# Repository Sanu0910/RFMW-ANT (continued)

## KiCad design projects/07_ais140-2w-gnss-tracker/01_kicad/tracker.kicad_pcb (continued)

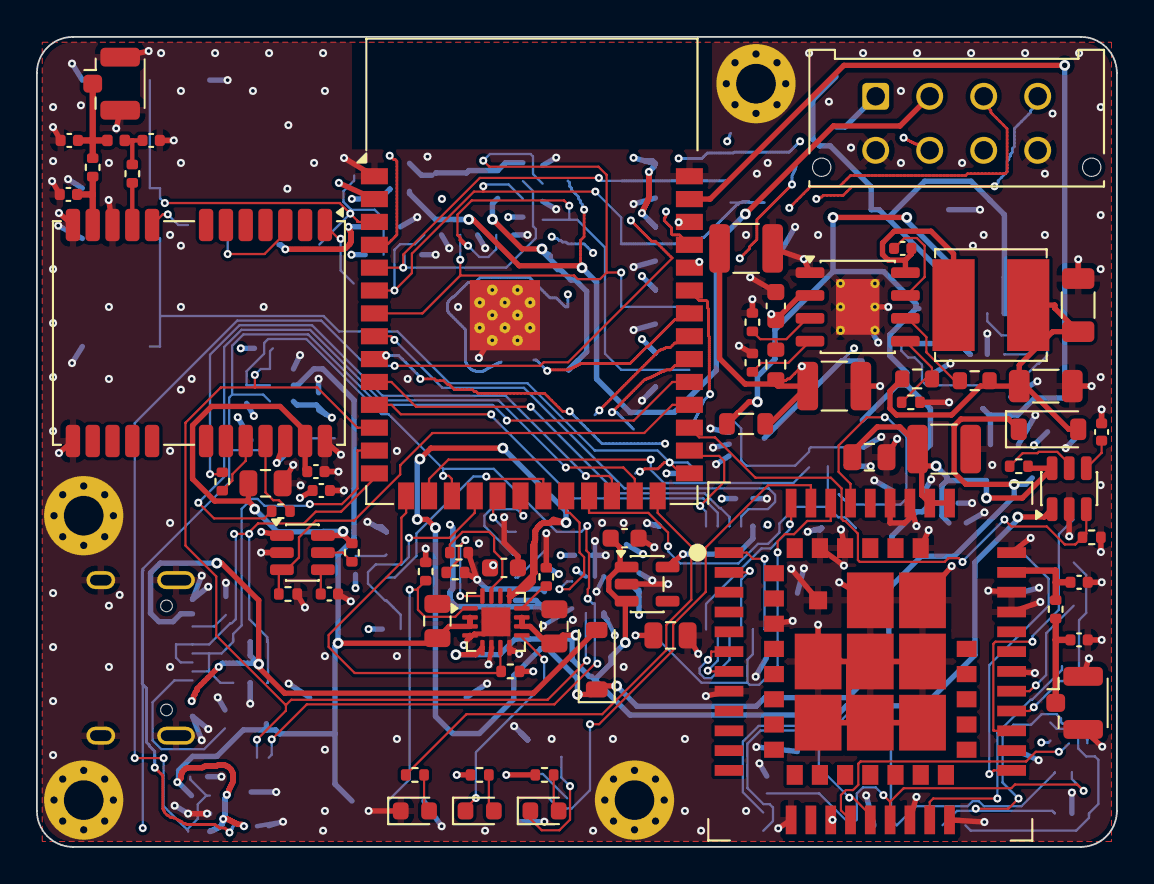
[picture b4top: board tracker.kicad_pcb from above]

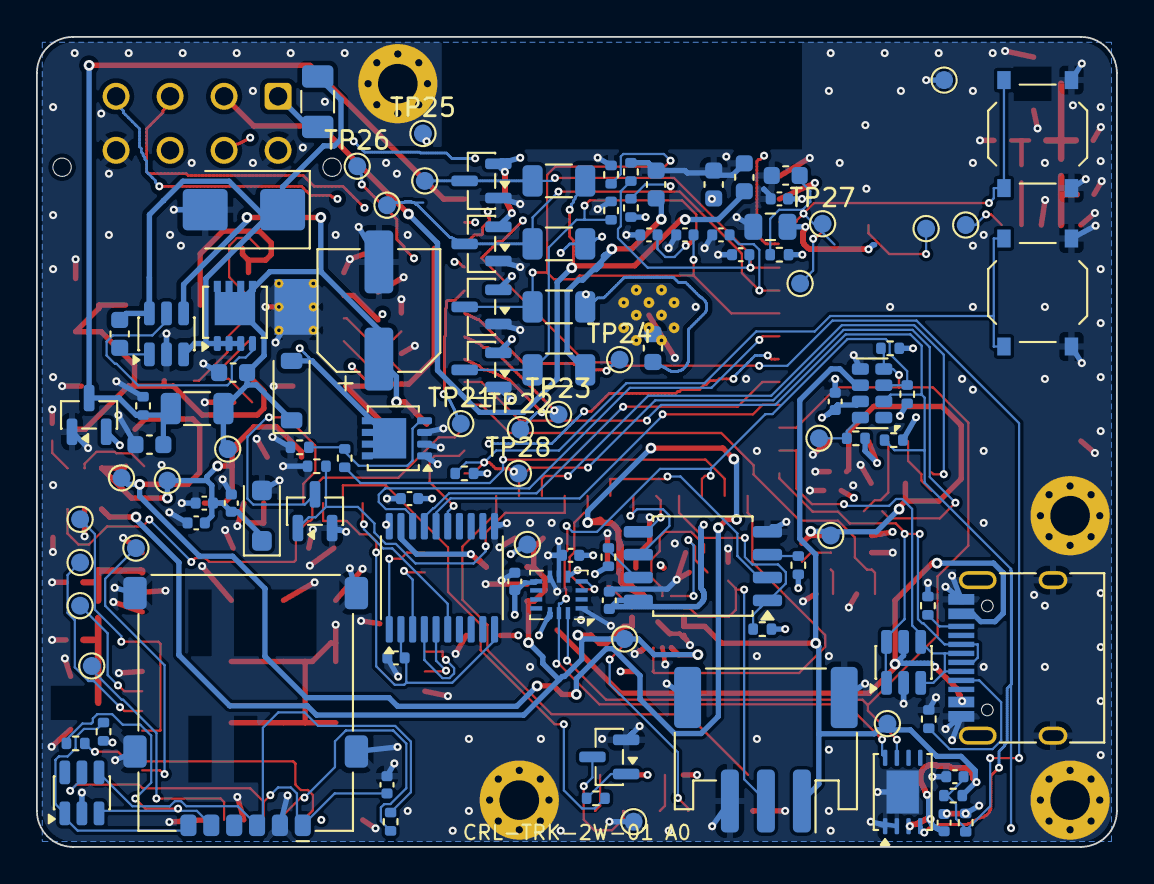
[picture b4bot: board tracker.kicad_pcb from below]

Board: 4 copper layers, 60.0 x 45.0 mm, 180 parts (111 on the bottom side), 114 nets.

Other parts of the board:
TP21: JTAG_TMS; TestPoint_Pad_D1.0mm
TP22: JTAG_TCK; TestPoint_Pad_D1.0mm
TP23: JTAG_TDO; TestPoint_Pad_D1.0mm
TP24: JTAG_TDI; TestPoint_Pad_D1.0mm
TP25: U0TXD; TestPoint_Pad_D1.0mm
TP26: U0RXD; TestPoint_Pad_D1.0mm
TP27: ESP_EN; TestPoint_Pad_D1.0mm
TP28: BOOT; TestPoint_Pad_D1.0mm

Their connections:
BOOT: TP28.1; also elsewhere on the board
ESP_EN: TP27.1; also elsewhere on the board
JTAG_TCK: TP22.1; also elsewhere on the board
JTAG_TDI: TP24.1; also elsewhere on the board
JTAG_TDO: TP23.1; also elsewhere on the board
JTAG_TMS: TP21.1; also elsewhere on the board
U0RXD: TP26.1; also elsewhere on the board
U0TXD: TP25.1; also elsewhere on the board

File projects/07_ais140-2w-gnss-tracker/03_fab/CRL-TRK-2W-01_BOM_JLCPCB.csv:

Comment,Designator,Footprint,LCSC Part #,Manufacturer Part Number
100nF/16V,C1,C_0603_1608Metric,,"0603 MLCC X7R/X5R, AEC-Q200"
100nF/100V,"C2,C6",C_0603_1608Metric,,"0603 MLCC X7R/X5R, AEC-Q200"
22uF/63V,C3,CP_Elec_6.3x7.7,,EEE-FK1J220P
2.2uF/100V,"C4,C5",C_1210_3225Metric,,"1210 MLCC X7R/X5R, AEC-Q200"
2.2nF/50V,C7,C_0402_1005Metric,,"0402 MLCC X7R/X5R, AEC-Q200"
22uF/10V,"C8,C9",C_1206_3216Metric,,"1206 MLCC X7R/X5R, AEC-Q200"
100nF,C10,C_0603_1608Metric,,"0603 MLCC X7R/X5R, AEC-Q200"
1uF/25V,C11,C_0603_1608Metric,,"0603 MLCC X7R/X5R, AEC-Q200"
10uF/10V,"C12,C17,C25,C34",C_0805_2012Metric,,"0805 MLCC X7R/X5R, AEC-Q200"
4.7uF/10V,C13,C_0805_2012Metric,,"0805 MLCC X7R/X5R, AEC-Q200"
100nF,"C14,C15,C21,C23,C26,C29,C30,C31,C35,C36,C40,C41,C42,C44,C46,C48,C50",C_0402_1005Metric,,"0402 MLCC X7R/X5R, AEC-Q200"
1uF/10V,C16,C_0603_1608Metric,,"0603 MLCC X7R/X5R, AEC-Q200"
1nF,"C18,C19",C_0402_1005Metric,,"0402 MLCC X7R/X5R, AEC-Q200"
22uF/10V,C20,C_0805_2012Metric,,"0805 MLCC X7R/X5R, AEC-Q200"
1uF,C22,C_0603_1608Metric,,"0603 MLCC X7R/X5R, AEC-Q200"
100uF/6.3V,C24,C_1210_3225Metric,,"1210 MLCC X7R/X5R, AEC-Q200"
33pF,C27,C_0402_1005Metric,,0402 C0G 50V
10pF,C28,C_0402_1005Metric,,0402 C0G 50V
10nF,C37,C_0402_1005Metric,,"0402 MLCC X7R/X5R, AEC-Q200"
10nF/100V,"C43,C45,C47,C49",C_0603_1608Metric,,"0603 MLCC X7R/X5R, AEC-Q200"
SMBJ33CA,D1,D_SMB,,SMBJ33CA
B5819W,"D2,D4",D_SOD-123,,B5819W
BAT54S,"D3,D9,D10,D11,D12",SOT-23,,BAT54S
GREEN,D5,LED_0603_1608Metric,,LTST-C191KGKT
RED,D6,LED_0603_1608Metric,,LTST-C191KRKT
SMF5.0A,D7,D_SOD-123F,,SMF5.0A
YELLOW,D8,LED_0603_1608Metric,,LTST-C191KSKT
1N4148W,D13,D_SOD-123,,1N4148W-7-F
2A,F1,Fuse_1206_3216Metric,,0466002.NRHF
600R@100M,FB1,L_0805_2012Metric,,BLM21PG601SN1D
VEHICLE 2x4,J1,Molex_Micro-Fit_3.0_43045-0812_2x04_P3.00mm_Vertical,,43045-0812
BATTERY 18650,J2,JST_PH_S3B-PH-SM4-TB_1x03-1MP_P2.00mm_Horizontal,,S3B-PH-SM4-TB(LF)(SN)
USB-C,J3,USB_C_Receptacle_HRO_TYPE-C-31-M-12,,TYPE-C-31-M-12
NANO-SIM,J5,nanoSIM_GCT_SIM8060-6-0-14-00,,SIM8060-6-0-14-00-A
LTE ANT,J6,U.FL_Hirose_U.FL-R-SMT-1_Vertical,,U.FL-R-SMT-1(10)
GNSS ANT,J7,U.FL_Hirose_U.FL-R-SMT-1_Vertical,,U.FL-R-SMT-1(10)
22uH,L1,L_Bourns_SRN6045TA,,SRN6045TA-220M
47nH,L2,L_0402_1005Metric,,LQG15HS47NJ02D
BUK7M12-60EX,Q1,LFPAK33,,BUK7M12-60EX
2N7002,Q2,SOT-23,,2N7002K-7
MMBT3904,Q3,SOT-23,,MMBT3904
BUK9M53-60EX,Q4,LFPAK33,,BUK9M53-60EX
1M,R1,R_0603_1608Metric,,"0603 1% thick film, AEC-Q200"
330k,R2,R_0402_1005Metric,,"0402 1% thick film, AEC-Q200"
160k,R3,R_0402_1005Metric,,"0402 1% thick film, AEC-Q200"
316k,R4,R_0603_1608Metric,,"0603 1% thick film, AEC-Q200"
100k,"R5,R14,R17,R18,R26,R50",R_0402_1005Metric,,"0402 1% thick film, AEC-Q200"
100k,R6,R_0603_1608Metric,,"0603 1% thick film, AEC-Q200"
1M,R7,R_1206_3216Metric,,"1206 1% thick film, AEC-Q200"
68k,R8,R_0402_1005Metric,,"0402 1% thick film, AEC-Q200"
1.5k,R9,R_0402_1005Metric,,"0402 1% thick film, AEC-Q200"
1.78k,R10,R_0402_1005Metric,,"0402 1% thick film, AEC-Q200"
15k,R11,R_0402_1005Metric,,"0402 1% thick film, AEC-Q200"
1M,"R15,R16",R_0402_1005Metric,,"0402 1% thick film, AEC-Q200"
10k,"R19,R20,R23,R37,R40,R48,R53,R54",R_0402_1005Metric,,"0402 1% thick film, AEC-Q200"
5.1k,"R21,R22",R_0402_1005Metric,,"0402 1% thick film, AEC-Q200"
1k,"R24,R25,R28,R33,R34",R_0402_1005Metric,,"0402 1% thick film, AEC-Q200"
4.7k,"R27,R38,R39",R_0402_1005Metric,,"0402 1% thick film, AEC-Q200"
22R,"R29,R30,R31",R_0402_1005Metric,,"0402 1% thick film, AEC-Q200"
0R,"R32,R36",R_0402_1005Metric,,0402 0R jumper
10R,R35,R_0402_1005Metric,,"0402 1% thick film, AEC-Q200"
100k,"R41,R45,R47",R_1206_3216Metric,,"1206 1% thick film, AEC-Q200"
22k,"R42,R46",R_0402_1005Metric,,"0402 1% thick film, AEC-Q200"
4.7k,R43,R_1206_3216Metric,,"1206 1% thick film, AEC-Q200"
47k,R44,R_0402_1005Metric,,"0402 1% thick film, AEC-Q200"
100R,"R49,R51,R52",R_0402_1005Metric,,"0402 1% thick film, AEC-Q200"
RESET,SW1,SW_Push_1P1T_XKB_TS-1187A,,TS-1187A-B-A-B
BOOT,SW2,SW_Push_1P1T_XKB_TS-1187A,,TS-1187A-B-A-B
LM74700-Q1,U1,SOT-23-6,,LM74700QDBVRQ1
LM5164-Q1,U2,HSOP-8-1EP_3.9x4.9mm_P1.27mm_EP2.41x3.1mm_ThermalVias,,LM5164QDDARQ1
BQ24074,U3,VQFN-16-1EP_3x3mm_P0.5mm_EP1.6x1.6mm,,BQ24074RGTR
LC709203F,U4,WDFN-8-1EP_4x3mm_P0.65mm_EP2.4x1.8mm,,LC709203FQH-01TWG
TLV75733P,U5,SOT-23-5,,TLV75733PDBVR
TPS22917,"U6,U7",SOT-23-6,,TPS22917DBVR
ESP32-S3-WROOM-1-N8R2,U8,ESP32-S3-WROOM-1_EdgeAntenna,,ESP32-S3-WROOM-1-N8R2
USBLC6-2SC6,U9,SOT-23-6,,USBLC6-2SC6
W25Q128JV,U10,SOIC-8_5.3x5.3mm_P1.27mm,,W25Q128JVSIQ
SIM7080G,U11,SIMCom_SIM7080G_LCC-77,,SIM7080G
TXS0108E,U12,TSSOP-20_4.4x6.5mm_P0.65mm,,TXS0108EPWR
ESDA6V1-5SC6,U13,SOT-23-6,,ESDA6V1-5SC6
NEO-F10N,U14,ublox_NEO,,NEO-F10N-00B
IIM-42652,U15,Bosch_LGA-14_3x2.5mm_P0.5mm,,IIM-42652
RV-3028-C7,U16,MicroCrystal_C7_SON-8_1.5x3.2mm_P0.9mm,,RV-3028-C7 32.768kHz 1ppm-TA-QC

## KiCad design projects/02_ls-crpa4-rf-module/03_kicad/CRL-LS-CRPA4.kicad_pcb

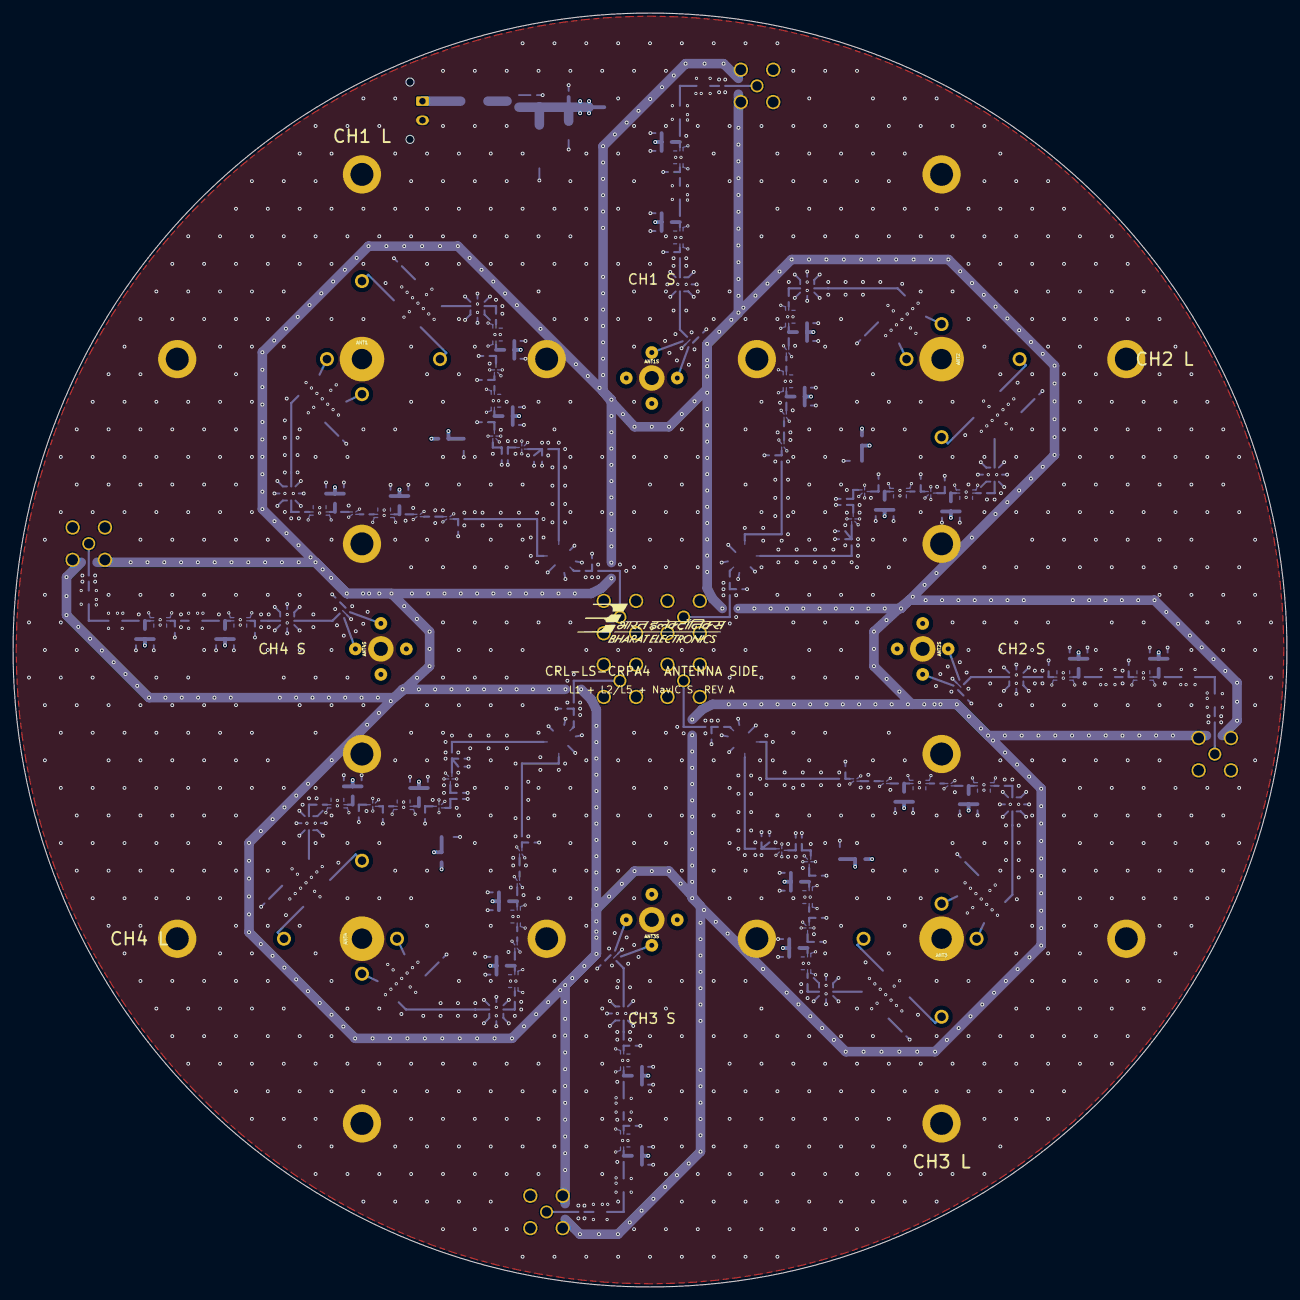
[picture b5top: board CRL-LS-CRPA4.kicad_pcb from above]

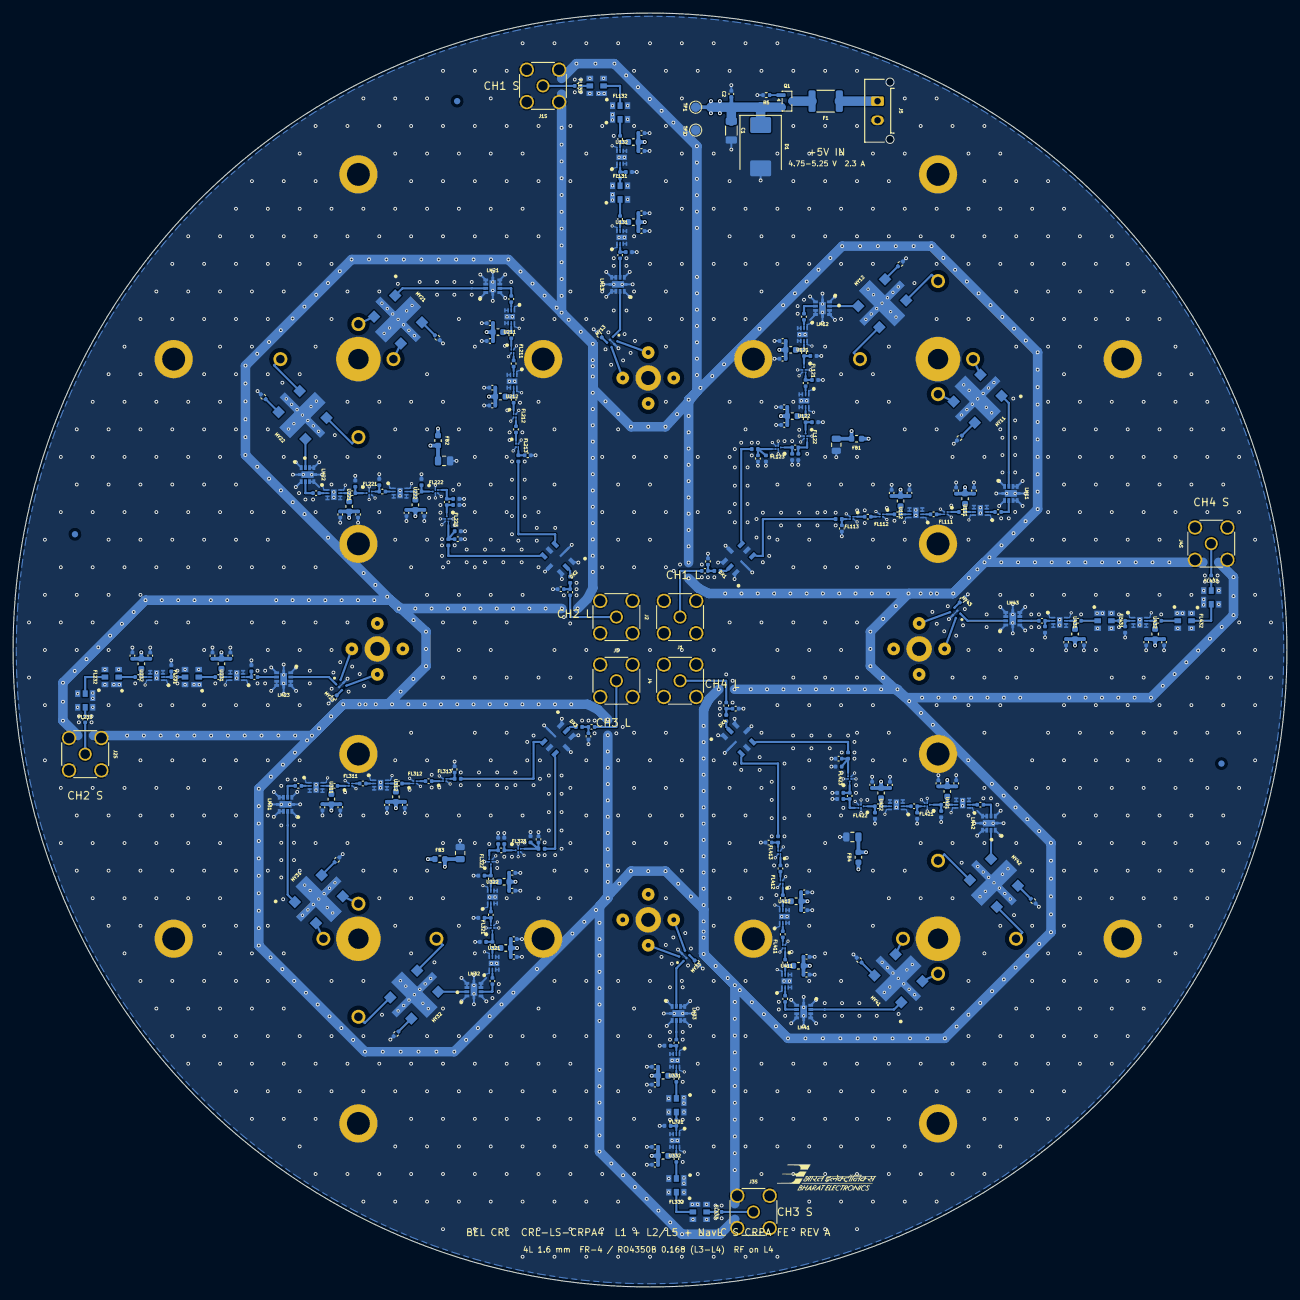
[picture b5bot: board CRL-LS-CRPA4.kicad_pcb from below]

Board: 4 copper layers, 200.0 x 200.0 mm, 331 parts (321 on the bottom side), 209 nets.

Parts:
ANT1, ANT2, ANT3, ANT4: L1/L2 stacked patch; GNSS_StackedPatch_L1L2_4feed
ANT1S, ANT2S, ANT3S, ANT4S: NavIC S patch; NavIC_S_Patch_4feed_combine_model
C1: 22uF; C_1206_3216Metric
C2: 100nF; C_0402_1005Metric
C135, C143, C235, C243, C335, C343, C435, C443, C1111, C1112, C1113, C1121, C1122, C1123, C1131, C1211, C1212, C1213, C1221, C1222, C1223, C1231, C1312, C1313, C1322, C1323, C2111, C2112, C2113, C2121, C2122, C2123, C2131, C2211, C2212, C2213, C2221, C2222, C2223, C2231, C2312, C2313, C2322, C2323, C3111, C3112, C3113, C3121, C3122, C3123, C3131, C3211, C3212, C3213, C3221, C3222, C3223, C3231, C3312, C3313, C3322, C3323, C4111, C4112, C4113, C4121, C4122, C4123, C4131, C4211, C4212, C4213, C4221, C4222, C4223, C4231, C4312, C4313, C4322, C4323: 100pF; C_0402_1005Metric
C141, C241, C341, C441: DNP; C_0402_1005Metric
C142, C242, C342, C442: 1.0pF; C_0402_1005Metric
C144, C244, C344, C444: 1.5pF; C_0402_1005Metric
C190, C290, C390, C490: 10uF; C_0805_2012Metric
C1114, C1124, C1214, C1224, C1314, C1324, C2114, C2124, C2214, C2224, C2314, C2324, C3114, C3124, C3214, C3224, C3314, C3324, C4114, C4124, C4214, C4224, C4314, C4324: 1uF; C_0402_1005Metric
C1311, C1321, C2311, C2321, C3311, C3321, C4311, C4321: 2.4pF; C_0402_1005Metric
D1: 1.5SMC6.8A; D_SMC
DX1, DX2, DX3, DX4: DXP.02.A
F1: 2A hold; Fuse_1812_4532Metric
FB1, FB2, FB3, FB4: 600R@100MHz; L_0603_1608Metric
FID1, FID2, FID3: Fiducial_1mm_Mask2mm
FL111, FL112, FL113, FL211, FL212, FL213, FL311, FL312, FL313, FL411, FL412, FL413: B7504; B7504_SAW_0.9x0.7
FL121, FL122, FL123, FL221, FL222, FL223, FL321, FL322, FL323, FL421, FL422, FL423: B8889; B8889_SAW_1.1x0.9
FL131, FL132, FL133, FL231, FL232, FL233, FL331, FL332, FL333, FL431, FL432, FL433: TA1442A; TA1442A_SAW_3x3
HY11, HY12, HY21, HY22, HY31, HY32, HY41, HY42: HC125A
HY13, HY23, HY33, HY43: C2327J5003AHF; Xinger_C2327J5003AHF
J1, J1S, J2, J2S, J3, J3S, J4, J4S: SMA; SMA_Amphenol_132134_Vertical
J5: +5V IN; Molex_Micro-Fit_3.0_43650-0215_1x02_P3.00mm_Vertical
L111, L112, L121, L122, L211, L212, L221, L222, L311, L312, L321, L322, L411, L412, L421, L422: 18nH; L_0603_1608Metric
L131, L132, L231, L232, L331, L332, L431, L432: 5.6nH; L_0603_1608Metric
L141, L241, L341, L441: 4.7nH; L_0402_1005Metric
L142, L242, L342, L442: 3.3nH; L_0402_1005Metric
L143, L243, L343, L443: 4.3nH; L_0402_1005Metric
L144, L244, L344, L444, L1215, L1216, L1225, L1226, L1235, L2215, L2216, L2225, L2226, L2235, L3215, L3216, L3225, L3226, L3235, L4215, L4216, L4225, L4226, L4235: 6.8nH; L_0402_1005Metric
L1317, L1327, L2317, L2327, L3317, L3327, L4317, L4327: 2.7nH; L_0402_1005Metric
LM11, LM12, LM13, LM21, LM22, LM23, LM31, LM32, LM33, LM41, LM42, LM43: CLM-83-2W+; MiniCircuits_DL1721
LOGOB: BEL_Logo_Silk_Small
LOGOT: BEL_Logo_Silk
MASKT: (no value)
Q1: AO3401A; SOT-23
R5: 10k; R_0402_1005Metric
R11, R12, R13, R21, R22, R23, R31, R32, R33, R41, R42, R43: 49.9R; R_0402_1005Metric
TP1, TP2: TP; TestPoint_Pad_D1.5mm
U111, U112, U121, U122, U131, U132, U211, U212, U221, U222, U231, U232, U311, U312, U321, U322, U331, U332, U411, U412, U421, U422, U431, U432: TQP3M9037; TQP3M9037_DFN8_2x2

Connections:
+5V: C1.1, C2.1, D1.1, FB1.1, FB2.1, FB3.1, FB4.1, Q1.2, TP1.1
+5V_CH1: C190.1, C1113.1, C1114.1, C1123.1, C1124.1, C1213.1, C1214.1, C1223.1, C1224.1, C1313.1, C1314.1, C1323.1, C1324.1, FB1.2, L111.2, L112.2, L121.2, L122.2, L131.2, L132.2
+5V_CH2: C290.1, C2113.1, C2114.1, C2123.1, C2124.1, C2213.1, C2214.1, C2223.1, C2224.1, C2313.1, C2314.1, C2323.1, C2324.1, FB2.2, L211.2, L212.2, L221.2, L222.2, L231.2, L232.2
+5V_CH3: C390.1, C3113.1, C3114.1, C3123.1, C3124.1, C3213.1, C3214.1, C3223.1, C3224.1, C3313.1, C3314.1, C3323.1, C3324.1, FB3.2, L311.2, L312.2, L321.2, L322.2, L331.2, L332.2
+5V_CH4: C490.1, C4113.1, C4114.1, C4123.1, C4124.1, C4213.1, C4214.1, C4223.1, C4224.1, C4313.1, C4314.1, C4323.1, C4324.1, FB4.2, L411.2, L412.2, L421.2, L422.2, L431.2, L432.2
CH1_COM: DX1.2, L143.1
CH1_COM_M: C143.1, C144.1, L143.2
CH1_L1_A1IN: C1111.2, U111.2
CH1_L1_A1OUT: C1112.1, L111.1, U111.7
CH1_L1_A1OUTC: C1112.2, FL111.1
CH1_L1_A2IN: C1121.2, U112.2
CH1_L1_A2OUT: C1122.1, L112.1, U112.7
CH1_L1_A2OUTC: C1122.2, FL112.1
CH1_L1_DXP: DX1.7, L141.2
CH1_L1_F0: ANT1.L1_0, HY11.4
CH1_L1_F90: ANT1.L1_90, HY11.3
CH1_L1_HYB: HY11.1, LM11.2
CH1_L1_ISO: HY11.2, R11.1
CH1_L1_LIM: C1111.1, LM11.7
CH1_L1_S1OUT: C1121.1, FL111.3
CH1_L1_S2OUT: C1131.1, FL112.3
CH1_L1_S3IN: C1131.2, FL113.1
CH1_L1_S3OUT: C141.1, FL113.3, L141.1
CH1_L2_A1IN: C1211.2, U121.2
CH1_L2_A1OUT: C1212.1, L121.1, U121.7
CH1_L2_A1OUTC: C1212.2, FL121.1, L1215.1
CH1_L2_A2IN: C1221.2, U122.2
CH1_L2_A2OUT: C1222.1, L122.1, U122.7
CH1_L2_A2OUTC: C1222.2, FL122.1, L1225.1
CH1_L2_DXP: DX1.5, L142.2
CH1_L2_F0: ANT1.L2_0, HY12.3
CH1_L2_F90: ANT1.L2_90, HY12.4
CH1_L2_HYB: HY12.1, LM12.2
CH1_L2_ISO: HY12.2, R12.1
CH1_L2_LIM: C1211.1, LM12.7
CH1_L2_S1OUT: C1221.1, FL121.4, L1216.1
CH1_L2_S2OUT: C1231.1, FL122.4, L1226.1
CH1_L2_S3IN: C1231.2, FL123.1, L1235.1
CH1_L2_S3OUT: C142.1, FL123.4, L142.1, L144.1
CH1_RFOUT: C143.2, J1.1
CH1_S_A1IN: C1311.2, L1317.1, U131.2
CH1_S_A1OUT: C1312.1, L131.1, U131.7
CH1_S_A1OUTC: C1312.2, FL131.2
CH1_S_A2IN: C1321.2, L1327.1, U132.2
CH1_S_A2OUT: C1322.1, L132.1, U132.7
CH1_S_A2OUTC: C1322.2, FL132.2
CH1_S_F0: ANT1S.F0, HY13.4
CH1_S_F90: ANT1S.F90, HY13.6
CH1_S_HYB: HY13.1, LM13.2
CH1_S_ISO: HY13.3, R13.1
CH1_S_LIM: C1311.1, LM13.7
CH1_S_RFOUT: C135.2, J1S.1
CH1_S_S1OUT: C1321.1, FL131.5
CH1_S_S2OUT: FL132.5, FL133.2
CH1_S_S3OUT: C135.1, FL133.5
CH2_COM: DX2.2, L243.1
CH2_COM_M: C243.1, C244.1, L243.2
CH2_L1_A1IN: C2111.2, U211.2
CH2_L1_A1OUT: C2112.1, L211.1, U211.7
CH2_L1_A1OUTC: C2112.2, FL211.1
CH2_L1_A2IN: C2121.2, U212.2
CH2_L1_A2OUT: C2122.1, L212.1, U212.7
CH2_L1_A2OUTC: C2122.2, FL212.1
CH2_L1_DXP: DX2.7, L241.2
CH2_L1_F0: ANT2.L1_0, HY21.4
CH2_L1_F90: ANT2.L1_90, HY21.3
CH2_L1_HYB: HY21.1, LM21.2
CH2_L1_ISO: HY21.2, R21.1
CH2_L1_LIM: C2111.1, LM21.7
CH2_L1_S1OUT: C2121.1, FL211.3
CH2_L1_S2OUT: C2131.1, FL212.3
CH2_L1_S3IN: C2131.2, FL213.1
CH2_L1_S3OUT: C241.1, FL213.3, L241.1
CH2_L2_A1IN: C2211.2, U221.2
CH2_L2_A1OUT: C2212.1, L221.1, U221.7
CH2_L2_A1OUTC: C2212.2, FL221.1, L2215.1
CH2_L2_A2IN: C2221.2, U222.2
CH2_L2_A2OUT: C2222.1, L222.1, U222.7
CH2_L2_A2OUTC: C2222.2, FL222.1, L2225.1
CH2_L2_DXP: DX2.5, L242.2
CH2_L2_F0: ANT2.L2_0, HY22.3
CH2_L2_F90: ANT2.L2_90, HY22.4
CH2_L2_HYB: HY22.1, LM22.2
CH2_L2_ISO: HY22.2, R22.1
CH2_L2_LIM: C2211.1, LM22.7
CH2_L2_S1OUT: C2221.1, FL221.4, L2216.1
CH2_L2_S2OUT: C2231.1, FL222.4, L2226.1
CH2_L2_S3IN: C2231.2, FL223.1, L2235.1
CH2_L2_S3OUT: C242.1, FL223.4, L242.1, L244.1
CH2_RFOUT: C243.2, J2.1
CH2_S_A1IN: C2311.2, L2317.1, U231.2
CH2_S_A1OUT: C2312.1, L231.1, U231.7
CH2_S_A1OUTC: C2312.2, FL231.2
CH2_S_A2IN: C2321.2, L2327.1, U232.2
CH2_S_A2OUT: C2322.1, L232.1, U232.7
CH2_S_A2OUTC: C2322.2, FL232.2
CH2_S_F0: ANT2S.F0, HY23.4
CH2_S_F90: ANT2S.F90, HY23.6
CH2_S_HYB: HY23.1, LM23.2
CH2_S_ISO: HY23.3, R23.1
CH2_S_LIM: C2311.1, LM23.7
CH2_S_RFOUT: C235.2, J2S.1
CH2_S_S1OUT: C2321.1, FL231.5
CH2_S_S2OUT: FL232.5, FL233.2
CH2_S_S3OUT: C235.1, FL233.5
CH3_COM: DX3.2, L343.1
CH3_COM_M: C343.1, C344.1, L343.2
CH3_L1_A1IN: C3111.2, U311.2
CH3_L1_A1OUT: C3112.1, L311.1, U311.7
CH3_L1_A1OUTC: C3112.2, FL311.1
CH3_L1_A2IN: C3121.2, U312.2
CH3_L1_A2OUT: C3122.1, L312.1, U312.7
CH3_L1_A2OUTC: C3122.2, FL312.1
CH3_L1_DXP: DX3.7, L341.2
CH3_L1_F0: ANT3.L1_0, HY31.4
CH3_L1_F90: ANT3.L1_90, HY31.3
CH3_L1_HYB: HY31.1, LM31.2
CH3_L1_ISO: HY31.2, R31.1
CH3_L1_LIM: C3111.1, LM31.7
CH3_L1_S1OUT: C3121.1, FL311.3
CH3_L1_S2OUT: C3131.1, FL312.3
CH3_L1_S3IN: C3131.2, FL313.1
CH3_L1_S3OUT: C341.1, FL313.3, L341.1
CH3_L2_A1IN: C3211.2, U321.2
CH3_L2_A1OUT: C3212.1, L321.1, U321.7
CH3_L2_A1OUTC: C3212.2, FL321.1, L3215.1
CH3_L2_A2IN: C3221.2, U322.2
CH3_L2_A2OUT: C3222.1, L322.1, U322.7
CH3_L2_A2OUTC: C3222.2, FL322.1, L3225.1
CH3_L2_DXP: DX3.5, L342.2
CH3_L2_F0: ANT3.L2_0, HY32.3
CH3_L2_F90: ANT3.L2_90, HY32.4
CH3_L2_HYB: HY32.1, LM32.2
CH3_L2_ISO: HY32.2, R32.1
CH3_L2_LIM: C3211.1, LM32.7
CH3_L2_S1OUT: C3221.1, FL321.4, L3216.1
CH3_L2_S2OUT: C3231.1, FL322.4, L3226.1
CH3_L2_S3IN: C3231.2, FL323.1, L3235.1
CH3_L2_S3OUT: C342.1, FL323.4, L342.1, L344.1
CH3_RFOUT: C343.2, J3.1
CH3_S_A1IN: C3311.2, L3317.1, U331.2
CH3_S_A1OUT: C3312.1, L331.1, U331.7
CH3_S_A1OUTC: C3312.2, FL331.2
CH3_S_A2IN: C3321.2, L3327.1, U332.2
CH3_S_A2OUT: C3322.1, L332.1, U332.7
CH3_S_A2OUTC: C3322.2, FL332.2
CH3_S_F0: ANT3S.F0, HY33.4
CH3_S_F90: ANT3S.F90, HY33.6
CH3_S_HYB: HY33.1, LM33.2
CH3_S_ISO: HY33.3, R33.1
CH3_S_LIM: C3311.1, LM33.7
CH3_S_RFOUT: C335.2, J3S.1
CH3_S_S1OUT: C3321.1, FL331.5
CH3_S_S2OUT: FL332.5, FL333.2
CH3_S_S3OUT: C335.1, FL333.5
CH4_COM: DX4.2, L443.1
CH4_COM_M: C443.1, C444.1, L443.2
CH4_L1_A1IN: C4111.2, U411.2
CH4_L1_A1OUT: C4112.1, L411.1, U411.7
CH4_L1_A1OUTC: C4112.2, FL411.1
CH4_L1_A2IN: C4121.2, U412.2
CH4_L1_A2OUT: C4122.1, L412.1, U412.7
CH4_L1_A2OUTC: C4122.2, FL412.1
CH4_L1_DXP: DX4.7, L441.2
CH4_L1_F0: ANT4.L1_0, HY41.4
CH4_L1_F90: ANT4.L1_90, HY41.3
CH4_L1_HYB: HY41.1, LM41.2
CH4_L1_ISO: HY41.2, R41.1
CH4_L1_LIM: C4111.1, LM41.7
CH4_L1_S1OUT: C4121.1, FL411.3
CH4_L1_S2OUT: C4131.1, FL412.3
CH4_L1_S3IN: C4131.2, FL413.1
CH4_L1_S3OUT: C441.1, FL413.3, L441.1
CH4_L2_A1IN: C4211.2, U421.2
CH4_L2_A1OUT: C4212.1, L421.1, U421.7
CH4_L2_A1OUTC: C4212.2, FL421.1, L4215.1
CH4_L2_A2IN: C4221.2, U422.2
CH4_L2_A2OUT: C4222.1, L422.1, U422.7
CH4_L2_A2OUTC: C4222.2, FL422.1, L4225.1
CH4_L2_DXP: DX4.5, L442.2
CH4_L2_F0: ANT4.L2_0, HY42.3
CH4_L2_F90: ANT4.L2_90, HY42.4
CH4_L2_HYB: HY42.1, LM42.2
CH4_L2_ISO: HY42.2, R42.1
CH4_L2_LIM: C4211.1, LM42.7
CH4_L2_S1OUT: C4221.1, FL421.4, L4216.1
CH4_L2_S2OUT: C4231.1, FL422.4, L4226.1
CH4_L2_S3IN: C4231.2, FL423.1, L4235.1
CH4_L2_S3OUT: C442.1, FL423.4, L442.1, L444.1
CH4_RFOUT: C443.2, J4.1
CH4_S_A1IN: C4311.2, L4317.1, U431.2
CH4_S_A1OUT: C4312.1, L431.1, U431.7
CH4_S_A1OUTC: C4312.2, FL431.2
CH4_S_A2IN: C4321.2, L4327.1, U432.2
CH4_S_A2OUT: C4322.1, L432.1, U432.7
CH4_S_A2OUTC: C4322.2, FL432.2
CH4_S_F0: ANT4S.F0, HY43.4
CH4_S_F90: ANT4S.F90, HY43.6
CH4_S_HYB: HY43.1, LM43.2
CH4_S_ISO: HY43.3, R43.1
CH4_S_LIM: C4311.1, LM43.7
CH4_S_RFOUT: C435.2, J4S.1
CH4_S_S1OUT: C4321.1, FL431.5
CH4_S_S2OUT: FL432.5, FL433.2
CH4_S_S3OUT: C435.1, FL433.5
GND: ANT1.C, ANT1.M, ANT1S.C, ANT2.C, ANT2.M, ANT2S.C, ANT3.C, ANT3.M, ANT3S.C, ANT4.C, ANT4.M, ANT4S.C, C1.2, C2.2, C141.2, C142.2, C144.2, C190.2, C241.2, C242.2, C244.2, C290.2, C341.2, C342.2, C344.2, C390.2, C441.2, C442.2, C444.2, C490.2, C1113.2, C1114.2, C1123.2, C1124.2, C1213.2, C1214.2, C1223.2, C1224.2, C1313.2, C1314.2, C1323.2, C1324.2, C2113.2, C2114.2, C2123.2, C2124.2, C2213.2, C2214.2, C2223.2, C2224.2, C2313.2, C2314.2, C2323.2, C2324.2, C3113.2, C3114.2, C3123.2, C3124.2, C3213.2, C3214.2, C3223.2, C3224.2, C3313.2, C3314.2, C3323.2, C3324.2, C4113.2, C4114.2, C4123.2, C4124.2, C4213.2, C4214.2, C4223.2, C4224.2, C4313.2, C4314.2, C4323.2, C4324.2, D1.2, DX1.1, DX1.3, DX1.4, DX1.6, DX1.8, DX2.1, DX2.3, DX2.4, DX2.6, DX2.8, DX3.1, DX3.3, DX3.4, DX3.6, DX3.8, DX4.1, DX4.3, DX4.4, DX4.6, DX4.8, FL111.2, FL111.4, FL112.2, FL112.4, FL113.2, FL113.4, FL121.2, FL121.3, FL121.5, FL122.2, FL122.3, FL122.5, FL123.2, FL123.3, FL123.5, FL131.1, FL131.3, FL131.4, FL131.6, FL132.1, FL132.3, FL132.4, FL132.6, FL133.1, FL133.3, FL133.4, FL133.6, FL211.2, FL211.4, FL212.2, FL212.4, FL213.2, FL213.4, FL221.2, FL221.3, FL221.5, FL222.2, FL222.3, FL222.5, FL223.2, FL223.3, FL223.5, FL231.1, FL231.3, FL231.4, FL231.6, FL232.1, FL232.3, FL232.4, FL232.6, FL233.1, FL233.3, FL233.4, FL233.6, FL311.2, FL311.4, FL312.2, FL312.4, FL313.2, FL313.4, FL321.2, FL321.3, FL321.5, FL322.2, FL322.3, FL322.5, FL323.2, FL323.3, FL323.5, FL331.1, FL331.3, FL331.4, FL331.6, FL332.1, FL332.3, FL332.4, FL332.6, FL333.1, FL333.3, FL333.4, FL333.6, FL411.2, FL411.4, FL412.2, FL412.4, FL413.2, FL413.4, FL421.2, FL421.3, FL421.5, FL422.2, FL422.3, FL422.5, FL423.2, FL423.3, FL423.5, FL431.1, FL431.3, FL431.4, FL431.6, FL432.1, FL432.3, FL432.4, FL432.6, FL433.1, FL433.3, FL433.4, FL433.6, HY11.GND, HY12.GND, HY13.2, HY13.5, HY21.GND, HY22.GND, HY23.2, HY23.5, HY31.GND, HY32.GND, HY33.2, HY33.5, HY41.GND, HY42.GND, HY43.2, HY43.5, J1.2, J1S.2, J2.2, J2S.2, J3.2, J3S.2, J4.2, J4S.2, J5.2, L144.2, L244.2, L344.2, L444.2, L1215.2, L1216.2, L1225.2, L1226.2, L1235.2, L1317.2, L1327.2, L2215.2, L2216.2, L2225.2, L2226.2, L2235.2, L2317.2, L2327.2, L3215.2, L3216.2, L3225.2, L3226.2, L3235.2, L3317.2, L3327.2, L4215.2, L4216.2, L4225.2, L4226.2, L4235.2, L4317.2, L4327.2, LM11.1, LM11.3, LM11.4, LM11.5, LM11.6, LM11.8, LM11.9, LM12.1, LM12.3, LM12.4, LM12.5, LM12.6, LM12.8, LM12.9, LM13.1, LM13.3, LM13.4, LM13.5, LM13.6, LM13.8, LM13.9, LM21.1, LM21.3, LM21.4, LM21.5, LM21.6, LM21.8, LM21.9, LM22.1, LM22.3, LM22.4, LM22.5, LM22.6, LM22.8, LM22.9, LM23.1, LM23.3, LM23.4, LM23.5, LM23.6, LM23.8, LM23.9, LM31.1, LM31.3, LM31.4, LM31.5, LM31.6, LM31.8, LM31.9, LM32.1, LM32.3, LM32.4, LM32.5, LM32.6, LM32.8, LM32.9, LM33.1, LM33.3, LM33.4, LM33.5, LM33.6, LM33.8, LM33.9, LM41.1, LM41.3, LM41.4, LM41.5, LM41.6, LM41.8, LM41.9, LM42.1, LM42.3, LM42.4, LM42.5, LM42.6, LM42.8, LM42.9, LM43.1, LM43.3, LM43.4, LM43.5, LM43.6, LM43.8, LM43.9, R5.2, R11.2, R12.2, R13.2, R21.2, R22.2, R23.2, R31.2, R32.2, R33.2, R41.2, R42.2, R43.2, TP2.1, U111.1, U111.3, U111.4, U111.5, U111.6, U111.8, U111.9, U112.1, U112.3, U112.4, U112.5, U112.6, U112.8, U112.9, U121.1, U121.3, U121.4, U121.5, U121.6, U121.8, U121.9, U122.1, U122.3, U122.4, U122.5, U122.6, U122.8, U122.9, U131.1, U131.3, U131.4, U131.5, U131.6, U131.8, U131.9, U132.1, U132.3, U132.4, U132.5, U132.6, U132.8, U132.9, U211.1, U211.3, U211.4, U211.5, U211.6, U211.8, U211.9, U212.1, U212.3, U212.4, U212.5, U212.6, U212.8, U212.9, U221.1, U221.3, U221.4, U221.5, U221.6, U221.8, U221.9, U222.1, U222.3, U222.4, U222.5, U222.6, U222.8, U222.9, U231.1, U231.3, U231.4, U231.5, U231.6, U231.8, U231.9, U232.1, U232.3, U232.4, U232.5, U232.6, U232.8, U232.9, U311.1, U311.3, U311.4, U311.5, U311.6, U311.8, U311.9, U312.1, U312.3, U312.4, U312.5, U312.6, U312.8, U312.9, U321.1, U321.3, U321.4, U321.5, U321.6, U321.8, U321.9, U322.1, U322.3, U322.4, U322.5, U322.6, U322.8, U322.9, U331.1, U331.3, U331.4, U331.5, U331.6, U331.8, U331.9, U332.1, U332.3, U332.4, U332.5, U332.6, U332.8, U332.9, U411.1, U411.3, U411.4, U411.5, U411.6, U411.8, U411.9, U412.1, U412.3, U412.4, U412.5, U412.6, U412.8, U412.9, U421.1, U421.3, U421.4, U421.5, U421.6, U421.8, U421.9, U422.1, U422.3, U422.4, U422.5, U422.6, U422.8, U422.9, U431.1, U431.3, U431.4, U431.5, U431.6, U431.8, U431.9, U432.1, U432.3, U432.4, U432.5, U432.6, U432.8, U432.9
QG: Q1.1, R5.1
VIN: F1.1, J5.1
VIN_F: F1.2, Q1.3

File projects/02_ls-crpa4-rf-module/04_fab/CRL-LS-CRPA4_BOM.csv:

item,qty,refs,value,mpn,manufacturer,footprint,side,description
1,4,C142 C242 C342 C442,1.0pF,GJM1555C1H1R0BB01D,Murata,C_0402_1005Metric,bottom,C0G hi-Q 0402
2,4,C144 C244 C344 C444,1.5pF,GJM1555C1H1R5BB01D,Murata,C_0402_1005Metric,bottom,C0G hi-Q 0402
3,8,C1311 C1321 C2311 C2321 C3311 C3321 C4311 C4321,2.4pF,GJM1555C1H2R4BB01D,Murata,C_0402_1005Metric,bottom,"C0G hi-Q 0402, S LNA input series (Qorvo 2.3-2.6 GHz ref. design)"
4,80,C1111 C1112 C1113 C1121 C1122 C1123 C1131 C1211 C1212 C1213 C1221 C1222 C1223 C1231 C1312 C1313 C1322 C1323 C135 C143 C2111 C2112 C2113 C2121 C2122 C2123 C2131 C2211 C2212 C2213 C2221 C2222 C2223 C2231 C2312 C2313 C2322 C2323 C235 C243 C3111 C3112 C3113 C3121 C3122 C3123 C3131 C3211 C3212 C3213 C3221 C3222 C3223 C3231 C3312 C3313 C3322 C3323 C335 C343 C4111 C4112 C4113 C4121 C4122 C4123 C4131 C4211 C4212 C4213 C4221 C4222 C4223 C4231 C4312 C4313 C4322 C4323 C435 C443,100pF,GRM1555C1H101JA01D,Murata,C_0402_1005Metric,bottom,C0G 50 V 0402
5,24,C1114 C1124 C1214 C1224 C1314 C1324 C2114 C2124 C2214 C2224 C2314 C2324 C3114 C3124 C3214 C3224 C3314 C3324 C4114 C4124 C4214 C4224 C4314 C4324,1uF,GRM155R61A105KE15D,Murata,C_0402_1005Metric,bottom,X5R 10 V 0402
6,1,C2,100nF,GRM155R71C104KA88D,Murata,C_0402_1005Metric,bottom,X7R 16 V 0402
7,4,C190 C290 C390 C490,10uF,GRM21BR61A106KE19L,Murata,C_0805_2012Metric,bottom,X5R 10 V 0805
8,1,C1,22uF,GRM31CR61A226KE15L,Murata,C_1206_3216Metric,bottom,X5R 10 V 1206
9,1,D1,1.5SMC6.8A,1.5SMC6.8A,Littelfuse,D_SMC,bottom,"TVS 1500 W, 5.8 V standoff / 6.8 V breakdown, SMC (DO-214AB)"
10,4,DX1 DX2 DX3 DX4,DXP.02.A,DXP.02.A,Taoglas,DXP.02.A,bottom,GNSS diplexer L1 / L2-L5
11,12,FL121 FL122 FL123 FL221 FL222 FL223 FL321 FL322 FL323 FL421 FL422 FL423,B8889,B39122B8889P810,Qualcomm RF360,B8889_SAW_1.1x0.9,bottom,"SAW, GNSS L2/L5"
12,12,FL111 FL112 FL113 FL211 FL212 FL213 FL311 FL312 FL313 FL411 FL412 FL413,B7504,B39162B7504L210,Qualcomm RF360,B7504_SAW_0.9x0.7,bottom,"SAW, GNSS L1/B1/G1"
13,4,FB1 FB2 FB3 FB4,600R@100MHz,BLM18KG601SN1D,Murata,L_0603_1608Metric,bottom,"ferrite bead 1.3 A, per-channel bias isolation (star branch)"
14,1,F1,2A hold,MF-MSMF200-2,Bourns,Fuse_1812_4532Metric,bottom,resettable fuse 1812
15,12,FL131 FL132 FL133 FL231 FL232 FL233 FL331 FL332 FL333 FL431 FL432 FL433,TA1442A,TA1442A,Tai-Saw,TA1442A_SAW_3x3,bottom,"SAW 2492 MHz NavIC S, 3.0x3.0x1.4 mm, IL 1.55 dB, Pin max +10 dBm, DC max 3 V (Tai-Saw Rev 1 land pattern)"
16,4,HY13 HY23 HY33 HY43,C2327J5003AHF,C2327J5003AHF,TTM Technologies,Xinger_C2327J5003AHF,bottom,"Xinger 90 deg hybrid 2300-2700 MHz, IL 0.3 dB, iso 22 dB, 0.68 mm (TTM Rev K land pattern); config 1: F0 -> 4, F90 -> 6 = RHCP"
17,8,HY11 HY12 HY21 HY22 HY31 HY32 HY41 HY42,HC125A,HC125A,Taoglas,HC125A,bottom,90 deg hybrid coupler 1150-1630 MHz
18,8,J1 J1S J2 J2S J3 J3S J4 J4S,SMA,132134,Amphenol RF,SMA_Amphenol_132134_Vertical,bottom,"SMA jack, vertical PCB, 50 ohm (fitted on bottom)"
19,1,J5,+5V IN,43650-0215,Molex,Molex_Micro-Fit_3.0_43650-0215_1x02_P3.00mm_Vertical,bottom,"Micro-Fit 3.0, 2 pos, single DC bias input"
20,12,LM11 LM12 LM13 LM21 LM22 LM23 LM31 LM32 LM33 LM41 LM42 LM43,CLM-83-2W+,CLM-83-2W+,Mini-Circuits,MiniCircuits_DL1721,bottom,"RF limiter 30-8200 MHz, 2 W, +11.5 dBm out, DL1721 3x3 mm hermetic"
21,8,L1317 L1327 L2317 L2327 L3317 L3327 L4317 L4327,2.7nH,LQP15MN2N7B02D,Murata,L_0402_1005Metric,bottom,S LNA input shunt (Qorvo 2.3-2.6 GHz ref. design) [verify MPN]
22,4,L142 L242 L342 L442,3.3nH,LQW15AN3N3B00D,Murata,L_0402_1005Metric,bottom,DXP L2/L5 port series
23,4,L143 L243 L343 L443,4.3nH,LQW15AN4N3B00D,Murata,L_0402_1005Metric,bottom,DXP common port series
24,4,L141 L241 L341 L441,4.7nH,LQW15AN4N7B00D,Murata,L_0402_1005Metric,bottom,DXP L1 port series
25,24,L1215 L1216 L1225 L1226 L1235 L144 L2215 L2216 L2225 L2226 L2235 L244 L3215 L3216 L3225 L3226 L3235 L344 L4215 L4216 L4225 L4226 L4235 L444,6.8nH,LQW15AN6N8G00D,Murata,L_0402_1005Metric,bottom,B8889 shunt match
26,16,L111 L112 L121 L122 L211 L212 L221 L222 L311 L312 L321 L322 L411 L412 L421 L422,18nH,LQW18AN18NG00D,Murata,L_0603_1608Metric,bottom,"LNA bias choke (eval-board value), 0603 wirewound"
27,8,L131 L132 L231 L232 L331 L332 L431 L432,5.6nH,LQW18AN5N6D00D,Murata,L_0603_1608Metric,bottom,"S LNA bias choke (Qorvo 2.3-2.6 GHz ref. design), 0603 wirewound [verify MPN]"
28,1,Q1,AO3401A,AO3401A,Alpha & Omega,SOT-23,bottom,"P-MOSFET -30 V -4 A, reverse-polarity protection (1 G, 2 S, 3 D)"
29,1,R5,10k,ERJ-2RKF1002X,Panasonic,R_0402_1005Metric,bottom,P-FET gate
30,12,R11 R12 R13 R21 R22 R23 R31 R32 R33 R41 R42 R43,49.9R,ERJ-2RKF49R9X,Panasonic,R_0402_1005Metric,bottom,hybrid isolated-port load
31,2,TP1 TP2,TP,-,-,TestPoint_Pad_D1.5mm,bottom,test pad
32,24,U111 U112 U121 U122 U131 U132 U211 U212 U221 U222 U231 U232 U311 U312 U321 U322 U331 U332 U411 U412 U421 U422 U431 U432,TQP3M9037,TQP3M9037,Qorvo,TQP3M9037_DFN8_2x2,bottom,"LNA 0.4 dB NF, 5 V / 70 mA"
33,1,BC01,,CRL-LS-CRPA4-BC01,project 02 drawing,06_step/CRL-LS-CRPA4-BC01.step,assembly,"Back cover L+S, Al 6061-T6, chromate conversion MIL-DTL-5541 Ty II Cl 3"
34,1,GSK1,,CHOFORM 5575 [ASSUMED],Parker Chomerics,mechanical,assembly,"Form-in-place conductive gasket on the BC01 wall tops, 0.8 mm bead, compressed to 0.30 mm"
35,4,ANT-L,,GPDF6010.A,Taoglas,mechanical,assembly,"L1/L2 stacked patch, fitted on top (customer supplied)"
36,4,ANT-S,,CRL-LS-SP01,BEL CRL (in-house),mechanical,assembly,"NavIC S patch 2492.028 MHz RHCP, <= 25 x 25 mm, 4 pins D0.77 at 4 mm + centre GND, lambda/2 spacing (r 42.53 mm)"
37,16,SCR1,,ISO 4762 M3x12 A2,-,mechanical,assembly,"Back cover -> board -> L patch, through the D3.6 M holes [ASSUMED length]"
38,4,SCR2,,ISO 4762 M2.5x6 A2,-,mechanical,assembly,DC receptacle flange
39,1,J-DC,,"[ASSUMED] flange receptacle, 2+ pins, IP67",Amphenol / Binder,mechanical,assembly,"Sealed DC input on BC01 (D16.2 cut-out, 20 mm square M2.5)"
40,1,W1,,Harness J-DC -> J5,-,mechanical,assembly,"Molex Micro-Fit 3.0 43645-0200 housing + 2 x 46235 crimps, AWG22, 60 mm"

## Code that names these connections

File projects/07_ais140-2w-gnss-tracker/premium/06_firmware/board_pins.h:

/* Auto-generated by 02_python/make_pins.py from design.py - do not edit. */
/* CRL-TRK-2W-01 rev A0 - ESP32-S3-WROOM-1-N8R2 GPIO map */
#pragma once

#define PIN_BOOT                    0   /* BOOT */
#define PIN_VIN_SENSE               1   /* VIN_SENSE */
#define PIN_VBAT_SENSE              2   /* VBAT_SENSE */
#define PIN_PGOOD_N                 3   /* PGOOD_N */
#define PIN_AIN1_SENSE              4   /* AIN1_SENSE */
#define PIN_IGN_DET                 5   /* IGN_DET */
#define PIN_PANIC_DET               6   /* PANIC_DET */
#define PIN_DIN1_DET                7   /* DIN1_DET */
#define PIN_I2C_SDA                 8   /* I2C_SDA */
#define PIN_I2C_SCL                 9   /* I2C_SCL */
#define PIN_FLASH_CS               10   /* FLASH_CS */
#define PIN_FLASH_MOSI             11   /* FLASH_MOSI */
#define PIN_FLASH_SCK              12   /* FLASH_SCK */
#define PIN_FLASH_MISO             13   /* FLASH_MISO */
#define PIN_IMU_INT                14   /* IMU_INT */
#define PIN_MCU_TX_MDM             15   /* MCU_TX_MDM */
#define PIN_MCU_RX_MDM             16   /* MCU_RX_MDM */
#define PIN_MDM_DTR_3V3            17   /* MDM_DTR_3V3 */
#define PIN_MDM_RI_3V3             18   /* MDM_RI_3V3 */
#define PIN_USB_DM                 19   /* USB_DM */
#define PIN_USB_DP                 20   /* USB_DP */
#define PIN_MDM_PWRKEY_CTL         21   /* MDM_PWRKEY_CTL */
#define PIN_MDM_STATUS_3V3         35   /* MDM_STATUS_3V3 */
#define PIN_MDM_PWR_EN             36   /* MDM_PWR_EN */
#define PIN_GNSS_PWR_EN            37   /* GNSS_PWR_EN */
#define PIN_ALERT_N                38   /* ALERT_N */
#define PIN_JTAG_TCK               39   /* JTAG_TCK */
#define PIN_JTAG_TDO               40   /* JTAG_TDO */
#define PIN_JTAG_TDI               41   /* JTAG_TDI */
#define PIN_JTAG_TMS               42   /* JTAG_TMS */
#define PIN_U0TXD                  43   /* U0TXD */
#define PIN_U0RXD                  44   /* U0RXD */
#define PIN_LED_STAT               45   /* LED_STAT */
#define PIN_DOUT1_CTL              46   /* DOUT1_CTL */
#define PIN_GNSS_TXD_MCU           47   /* GNSS_TXD_MCU */
#define PIN_GNSS_RXD_MCU           48   /* GNSS_RXD_MCU */

/* I2C addresses */
#define I2C_ADDR_IMU        0x68   /* IIM-42652, AD0 = GND */
#define I2C_ADDR_GAUGE      0x0B   /* LC709203F */
#define I2C_ADDR_RTC        0x52   /* RV-3028-C7 */

/* ADC scaling (ADC1, 12 dB attenuation) */
#define VIN_DIV             ((1000.0f + 68.0f) / 68.0f)   /* R7/R8 */
#define VBAT_DIV            2.0f                           /* R15/R16 */
#define AIN1_DIV            ((100.0f + 10.0f) / 10.0f)    /* R47/R48 */
#define IGN_DIV             ((100.0f + 22.0f) / 22.0f)    /* R41/R42 */

/* Active levels */
#define PANIC_ACTIVE_LEVEL  0
#define IGN_ACTIVE_LEVEL    1
#define MDM_PWRKEY_PULSE_MS 1100   /* SIM7080G power-on: PWRKEY low >= 1 s */
#define LED_STAT_ON         1

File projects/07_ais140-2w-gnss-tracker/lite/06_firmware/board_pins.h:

/* Auto-generated by 02_python/make_pins.py from design.py - do not edit. */
/* CRL-TRK-2W-L1 rev A0 - Quectel EC200U-CN (QuecOpen / QuecPython) pin map. VERIFY against the EC200U HD. */
#pragma once

/* module pin number, QuecOpen GPIO number */
#define PIN_IGN_DET_N           1   /* GPIO1 = module pin 27 (GPIO1) */
#define PIN_ACC_INT             2   /* GPIO2 = module pin 26 (GPIO2) */
#define PIN_GNSS_EN             3   /* GPIO3 = module pin 24 (GPIO3) */
#define PIN_RELAY_CTL           4   /* GPIO4 = module pin 25 (GPIO4) */

/* fixed-function pins */
/* pin 41 I2C_SCL     -> I2C_SCL */
/* pin 42 I2C_SDA     -> I2C_SDA */
/* pin 44 ADC1        -> VIN_SENSE */
/* pin 45 ADC0        -> VBAT_SENSE */
/* pin 67 MAIN_TXD    -> MDM_TX_1V8 */
/* pin 68 MAIN_RXD    -> MDM_RX_1V8 */
/* pin 61 STATUS      -> MDM_STATUS */
/* pin  6 NET_STATUS  -> NET_STATUS */
/* pin 21 PWRKEY      -> MDM_PWRKEY */
/* pin 20 RESET_N     -> MDM_RESET_N */

#define GNSS_UART           0      /* MAIN UART (pins 67/68), NMEA 9600 8N1 from L76K */
#define I2C_ADDR_ACC        0x18   /* LIS3DH, SA0 = GND */
#define ADC_VIN_CH          1      /* ADC1 */
#define ADC_VBAT_CH         0      /* ADC0 */
#define VIN_DIV             ((1000.0f + 33.0f) / 33.0f)   /* R5/R6 */
#define VBAT_DIV            ((300.0f + 100.0f) / 100.0f)  /* R7/R8 */
#define IGN_ACTIVE_LEVEL    0      /* IGN_DET_N low = ignition on */
#define RELAY_ACTIVE_LEVEL  1
#define GNSS_EN_ACTIVE      1

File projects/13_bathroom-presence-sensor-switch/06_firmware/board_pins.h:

/* SPS-24G-01  (SAMAY ELECTRONICS)  -  ATtiny13A pin map.
 * Generated to match 02_python/design.py. Fuse: internal 9.6 MHz RC, /8 off (CKDIV8=1 -> 1.2 MHz) is fine;
 * 4.8/9.6 MHz also OK. BOD at 2.7 V recommended. Program via J2 (AVR ISP) with MAINS DISCONNECTED.
 *
 * ATtiny13A SOIC-8:
 *   1 PB5/RESET   -> RESET / ISP            5 PB0/MOSI -> TRIAC_DRV (opto LED, via R1 330R) + ISP MOSI
 *   2 PB3/ADC3    -> DELAY_ADJ (trimmer)    6 PB1/MISO -> STATUS LED (D1, via R1k)          + ISP MISO
 *   3 PB4/ADC2    -> RADAR_OUT (LD2410B)    7 PB2/SCK  -> BUTTON (SW1, active-low)           + ISP SCK
 *   4 GND                                   8 VCC (+5V)
 */
#pragma once
#include <avr/io.h>

#define RADAR_OUT_PIN   PB4   /* input : HIGH = person present (LD2410B OUT, 3.3 V) */
#define DELAY_ADC_CH    3     /* ADC3 on PB3 : 10k trimmer, sets OFF delay 10 s..10 min */
#define TRIAC_PIN       PB0   /* output: HIGH = opto ON = lamp ON (zero-cross) */
#define LED_PIN         PB1   /* output: status/fault LED */
#define BUTTON_PIN      PB2   /* input : momentary override, active-low (10k pull-up on board) */

/* Timing */
#define DELAY_MIN_S      10UL      /* trimmer fully CCW  */
#define DELAY_MAX_S      600UL     /* trimmer fully CW (10 min) */
#define DEBOUNCE_MS      30
#define LONGPRESS_MS     800       /* long press = force OFF */
#define RADAR_FAULT_MS   30000UL   /* OUT stuck, no change, radar-not-responding heuristic (optional) */

/* Logic levels */
#define PRESENT          1         /* RADAR_OUT asserted level */
#define LED_ON_LEVEL     1
#define TRIAC_ON_LEVEL   1
#define BUTTON_ACTIVE    0         /* pressed = low */
